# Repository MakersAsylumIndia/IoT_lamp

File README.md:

# Mood_Lamp
Mood lamp for Innovation school.

There are three versions.
- The initial version uses an ESP8266, relay module and 230V AC filament lamp. Some details can be found in </documentation> directory.

- A modified version of the initial version uses ESP8266 and a RGB LED ring of WS2812 LED's. It eliminates the relay module and the potentially hazardous 230V wiring. CAD design is similar to old version.

- There are two new versions - one based on the ESP32 and another based on an Arduino Nano. Both versions use a LED ring of sixteen WS2812B RGB LEDs (neopixels). Assembly consists of only laser cut part	s without any additional mounting hardware such as screws.

- Earlier prototypes consisted of a hexagon design with outer shell using living hinges, an octagon design using a pair of interlocking cubes and four iterations of the latest version.

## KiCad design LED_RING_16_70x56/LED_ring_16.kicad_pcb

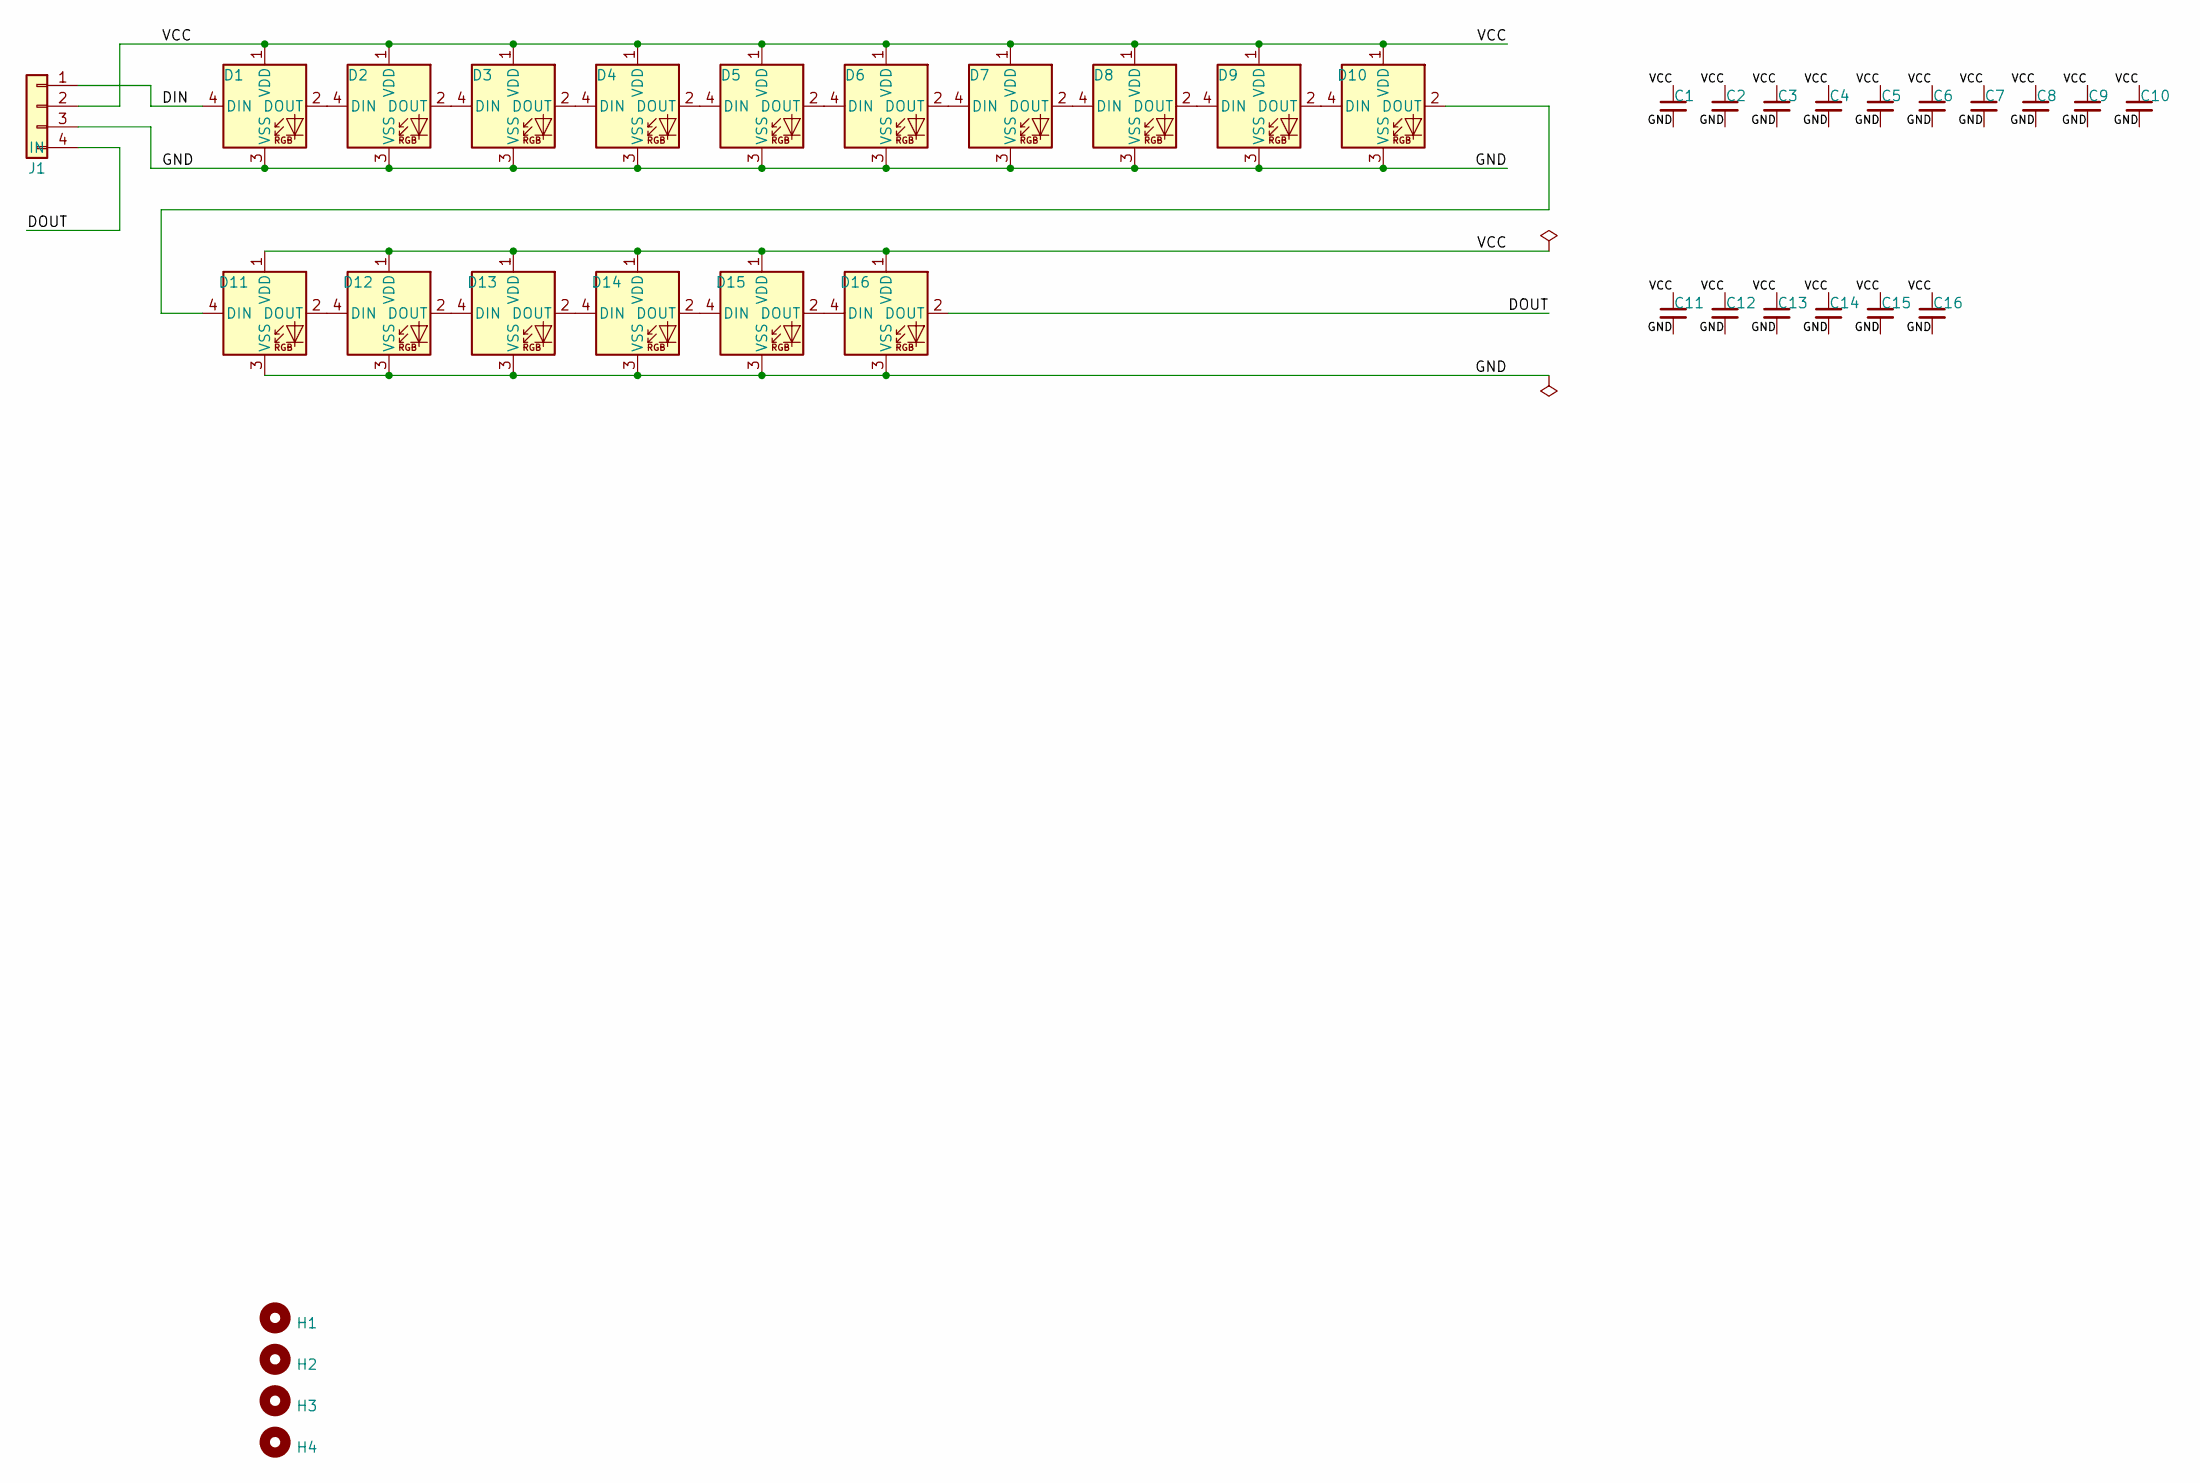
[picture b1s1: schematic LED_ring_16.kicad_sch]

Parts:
C1, C2, C3, C4, C5, C6, C7, C8, C9, C10, C11, C12, C13, C14, C15, C16: 100nF; C_0402_1005Metric
D1, D2, D3, D4, D5, D6, D7, D8, D9, D10, D11, D12, D13, D14, D15, D16: WS2812B; LED_WS2812B_PLCC4_5.0x5.0mm_P3.2mm
H1, H2, H3, H4: MountingHole; MountingHole_3mm
J1: IN; PinHeader_1x04_P1.27mm_Vertical_SMD_Pin1Left

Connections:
/DIN: D1.4 (DIN), J1.1
/DOUT: D16.2 (DOUT), J1.4
/GND: C1.2, C2.2, C3.2, C4.2, C5.2, C6.2, C7.2, C8.2, C9.2, C10.2, C11.2, C12.2, C13.2, C14.2, C15.2, C16.2, D1.3 (VSS), D2.3 (VSS), D3.3 (VSS), D4.3 (VSS), D5.3 (VSS), D6.3 (VSS), D7.3 (VSS), D8.3 (VSS), D9.3 (VSS), D10.3 (VSS), D11.3 (VSS), D12.3 (VSS), D13.3 (VSS), D14.3 (VSS), D15.3 (VSS), D16.3 (VSS), J1.3
/VCC: C1.1, C2.1, C3.1, C4.1, C5.1, C6.1, C7.1, C8.1, C9.1, C10.1, C11.1, C12.1, C13.1, C14.1, C15.1, C16.1, D1.1 (VDD), D2.1 (VDD), D3.1 (VDD), D4.1 (VDD), D5.1 (VDD), D6.1 (VDD), D7.1 (VDD), D8.1 (VDD), D9.1 (VDD), D10.1 (VDD), D11.1 (VDD), D12.1 (VDD), D13.1 (VDD), D14.1 (VDD), D15.1 (VDD), D16.1 (VDD), J1.2
unnamed: D1.2 (DOUT), D2.4 (DIN)
unnamed: D2.2 (DOUT), D3.4 (DIN)
unnamed: D3.2 (DOUT), D4.4 (DIN)
unnamed: D4.2 (DOUT), D5.4 (DIN)
unnamed: D5.2 (DOUT), D6.4 (DIN)
unnamed: D6.2 (DOUT), D7.4 (DIN)
unnamed: D7.2 (DOUT), D8.4 (DIN)
unnamed: D8.2 (DOUT), D9.4 (DIN)
unnamed: D9.2 (DOUT), D10.4 (DIN)
unnamed: D10.2 (DOUT), D11.4 (DIN)
unnamed: D11.2 (DOUT), D12.4 (DIN)
unnamed: D12.2 (DOUT), D13.4 (DIN)
unnamed: D13.2 (DOUT), D14.4 (DIN)
unnamed: D14.2 (DOUT), D15.4 (DIN)
unnamed: D15.2 (DOUT), D16.4 (DIN)

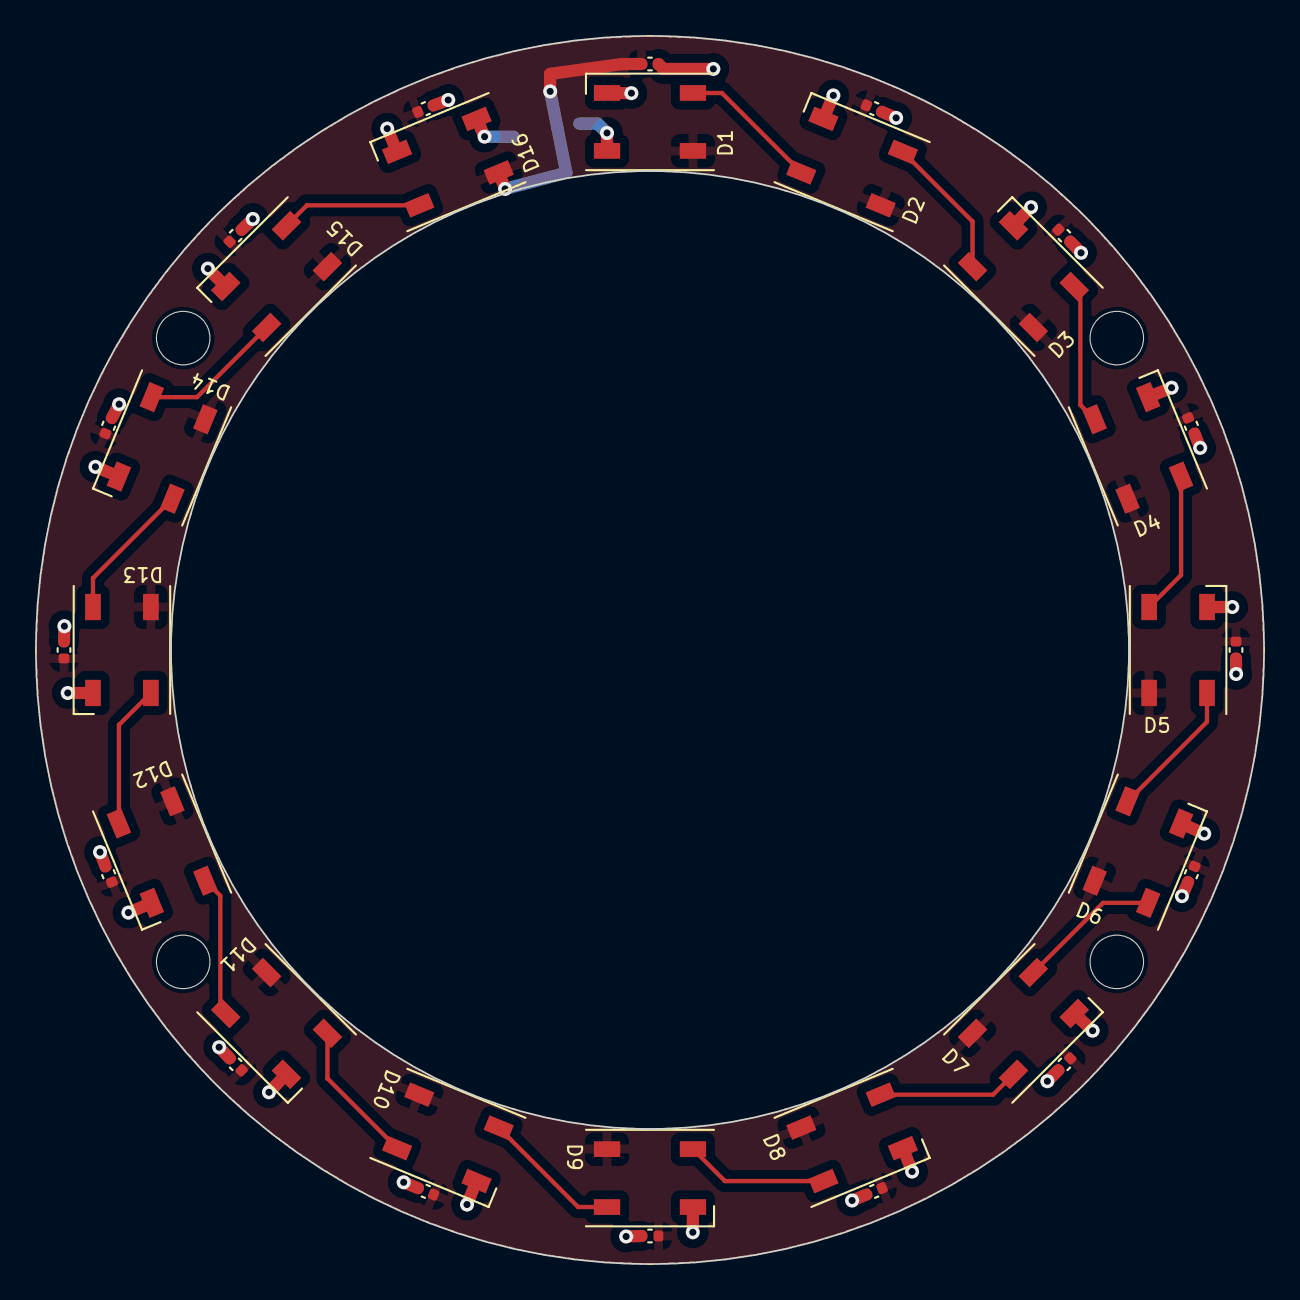
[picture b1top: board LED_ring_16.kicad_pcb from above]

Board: 2 copper layers, 70.0 x 70.0 mm, 37 parts (1 on the bottom side), 19 nets.

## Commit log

2023-07-03 octagon design ready
2023-07-11 octagon DXF in different thicknesses
2023-07-14 added locating slots for top and bottom
2023-07-23 new version, IoT_coaster lamp added
2023-08-02 improved fit
2023-08-05 modified mounting holes for ESP32 and slots for wiring
2023-08-10 added diffuser and assembly images
2023-08-12 new v3 version
2023-08-17 added alignment marks and minor mods
2023-09-13 modified LED ring holder
2023-09-14 added Nano version of Mood Lamp
2023-09-14 edited readme
2023-09-23 added assembly images
2023-09-25 added assembly animations
2023-09-25 added LED RING identifier image
2023-09-28 rearranged folders
2023-11-20 v3 of IoT mood lamp for better laser cutting
2023-11-30 minor edits
2023-11-30 reorganized all folders and added assembly images
2023-12-24 added image updates
2024-01-09 added changes suggested by Shivam
2024-02-24 modified LED PCB dimensions, created version v4
2024-09-09 updates based on MuSo feedback
2024-09-09 more updates based on MuSo feedback
2025-05-13 v4 IoT Moodlamp DXF laser cutting files set for 2.8mm
2025-09-25 added production DXF file
2025-09-25 modified production DXF file
2025-09-26 modified production DXF file v2
2026-01-06 top plate DXF
